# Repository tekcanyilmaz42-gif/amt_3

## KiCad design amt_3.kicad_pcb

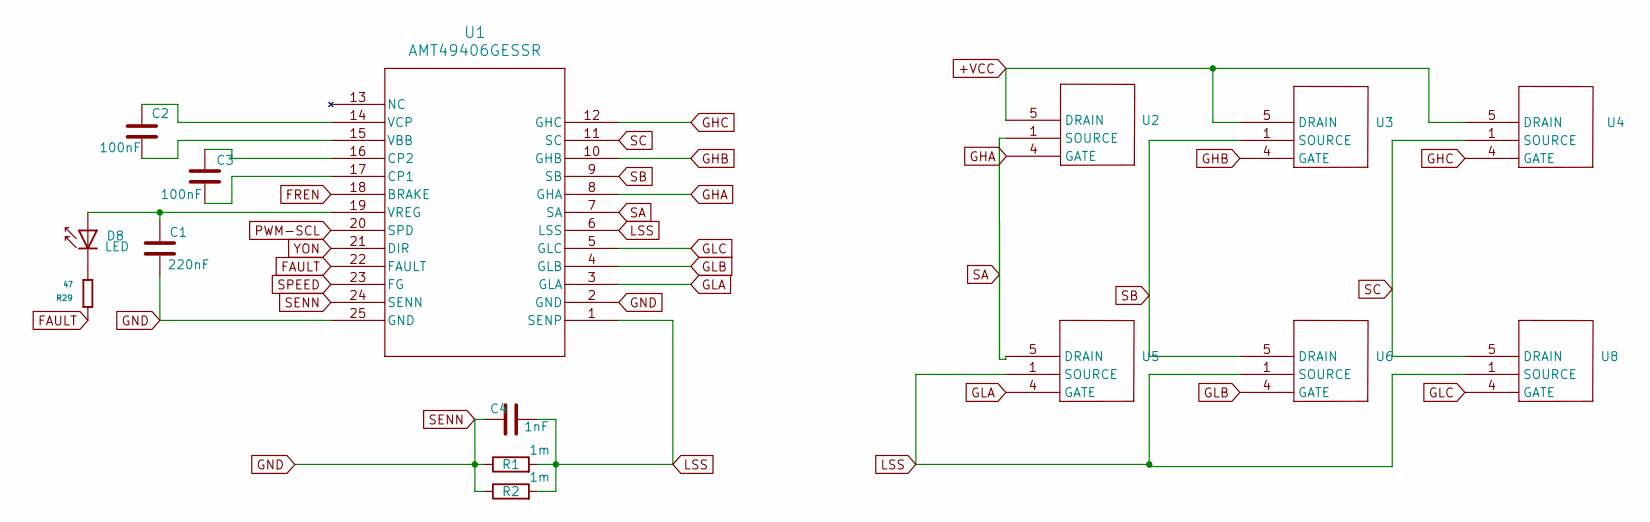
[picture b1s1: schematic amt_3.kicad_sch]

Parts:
C1: 220nF; C_0603_1608Metric_Pad1.08x0.95mm_HandSolder
C2, C3: 100nF; C_0603_1608Metric_Pad1.08x0.95mm_HandSolder
C4: 1nF; C_0603_1608Metric_Pad1.08x0.95mm_HandSolder
D8: LED; led; Digikey_Part_Number .
R1, R2: 1m; R_2512_6332Metric_Pad1.40x3.35mm_HandSolder
R29: 47; res
U1: AMT49406GESSR; amt49406
U2, U3, U4, U5, U6, U8: GT045N10D5

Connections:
+VCC: U2.5 (DRAIN), U3.5 (DRAIN), U4.5 (DRAIN)
FAULT: R29.2, U1.22 (FAULT)
FREN: U1.18 (BRAKE); also elsewhere on the board
GHA: U1.8 (GHA), U2.4 (GATE)
GHB: U1.10 (GHB), U3.4 (GATE)
GHC: U1.12 (GHC), U4.4 (GATE)
GLA: U1.3 (GLA), U5.4 (GATE)
GLB: U1.4 (GLB), U6.4 (GATE)
GLC: U1.5 (GLC), U8.4 (GATE)
GND: C1.2, C4.1, R1.1, R2.1, U1.2 (GND), U1.24 (SENN), U1.25 (GND)
LSS: C4.2, R1.2, R2.2, U1.1 (SENP), U1.6 (LSS), U5.1 (SOURCE), U6.1 (SOURCE), U8.1 (SOURCE)
unnamed: C1.1, D8.2 (A), U1.19 (VREG)
unnamed: D8.1 (K), R29.1
unnamed: C3.2, U1.17 (CP1)
unnamed: C3.1, U1.16 (CP2)
unnamed: C2.2, U1.15 (VBB)
unnamed: C2.1, U1.14 (VCP)
PWM-SCL: U1.20 (SPD); also elsewhere on the board
SA: U1.7 (SA), U2.1 (SOURCE), U5.5 (DRAIN)
SB: U1.9 (SB), U3.1 (SOURCE), U6.5 (DRAIN)
SC: U1.11 (SC), U4.1 (SOURCE), U8.5 (DRAIN)
SPEED: U1.23 (FG); also elsewhere on the board
YON: U1.21 (DIR); also elsewhere on the board

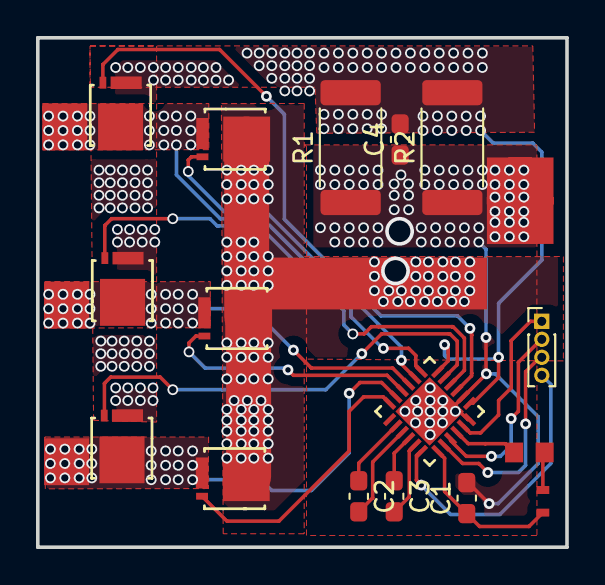
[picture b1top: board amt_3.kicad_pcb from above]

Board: 2 copper layers, 29.4 x 28.3 mm, 16 parts (0 on the bottom side), 23 nets.

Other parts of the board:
REF: PinHeader_1x04_P1.00mm_Vertical

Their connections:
FREN: REF.4; also elsewhere on the board
PWM-SCL: REF.3; also elsewhere on the board
SPEED: REF.1; also elsewhere on the board
YON: REF.2; also elsewhere on the board
